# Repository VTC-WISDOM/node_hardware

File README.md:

# hardware
a collection of schematic and pcb designs for the WiSDOM node
unless otherwise specified, everything contained in this repository is licensed under the CERN Open Hardware License version 2 - Weakly Reciprocal License (CERN-OHL-W).
this is comparable to the gpl2, see LICENSE for details

## Using this repo
using your favorite package manager, install kicad-footprints and kicad-symbols alongside kicad. this is the best way to get the standard libraries. if you for some reason cannot do so, see the linked official kicad libraries in kicad-libs/footprints and kicad-libs/symbols.
in the kicad symbol editor, go to preferences -> manage symbol libraries and select "add existing", navigate to the kicad-libs/symbols directory and select the symbol libraries contained therein. repeat this with the symbols contained in kicad-libs/JLCPCB-Kicad-Library.
repeat this for footprints.

### node-rp2040
stores all of the relevant design files for the WiSDOM node that is based on the RP2040

### node-rp2350
like above but the RP2350

### other
test projects, antenna and transmission equipment, etc. anything unspecified

### docs
will add as much documentation as possible!

## Node V6 (RP2040)

changes:
- removed 5v regulator
- changed rp2040 xtal to the recommended part due to availability
- changed the sim card slot due to availability
- reviewed other parts and made changes to ensure full availability from both JLC and Digikey
- changed footprints over to JLC library footprints
- major layout changes- pin headers now broken out in two halves, etc - look at the pcb for a full description
- removed jst connectors (evil) and replaced them with barrel jacks
- mounting holes now m2.5 instead of m2

## Node V5 (RP2040)
 ***SIM7080G NON-FUNCTIONAL***

change since previous version:
- added USBLC6 esd protection on the usb line
- added CAT24 eeprom ic
- removed options for rtc to stick with just the PCF8523
- added SP3485 for RS485 / MODBUS communication
- added u.fl connector for the ism radio
- changed to narrower profile pushbuttons for run/bootsel
- added additional reset switch to interrupt 3.3V to the board entirely (used to reset the device to a known state for all components including the radios)
- yet more improvements to routing
- updated design to be mostly assembled by JLC pcb fab available components

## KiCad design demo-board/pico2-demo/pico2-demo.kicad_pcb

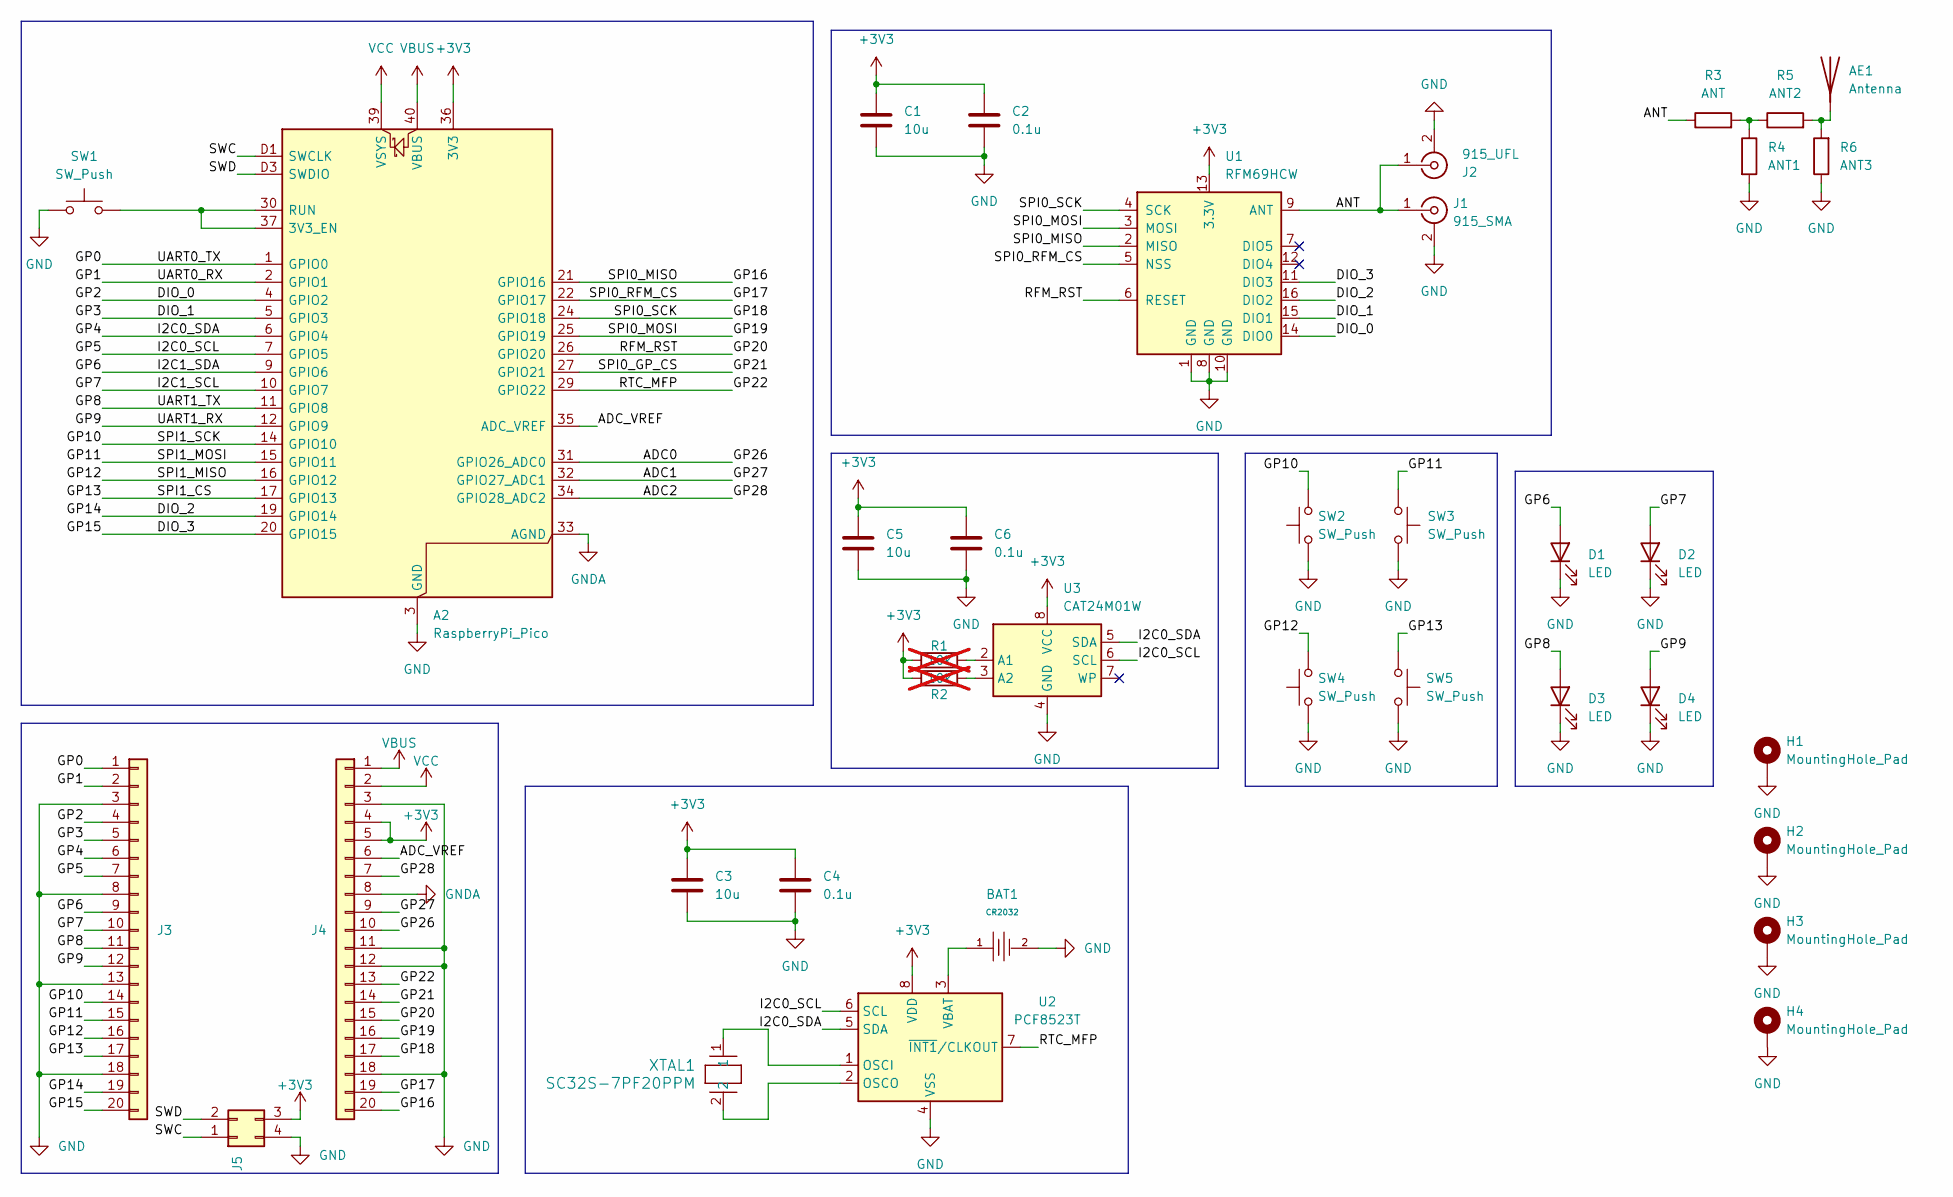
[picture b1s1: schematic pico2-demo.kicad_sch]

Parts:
A2: RaspberryPi_Pico; RaspberryPi_Pico_SMD_HandSolder
AE1: Antenna; Texas_SWRA416_868MHz_915MHz
BAT1: CR2032; BAT_BAT-HLD-001-THM; Part BS-07-A1BJ001; LCSC C2979167
C1, C3, C5: 10u; C_0805_2012Metric_Pad1.18x1.45mm_HandSolder
C2, C4, C6: 0.1u; C_0402_1005Metric_Pad0.74x0.62mm_HandSolder
D1, D2, D3, D4: LED; LED_1206_3216Metric_Pad1.42x1.75mm_HandSolder
H1, H2, H3: MountingHole_Pad; MountingHole_3.2mm_M3_Pad
H4: MountingHole_Pad; MountingHole_3.2mm_M3
J1: 915_SMA; SMA_Samtec_SMA-J-P-H-ST-EM1_EdgeMount
J2: 915_UFL; U.FL_Molex_MCRF_73412-0110_Vertical
J3, J4: Conn_01x20; PinHeader_1x20_P2.54mm_Vertical
J5: Conn_02x02_Counter_Clockwise; PinHeader_2x02_P2.54mm_Vertical
R1, R2: 10k; R_0805_2012Metric_Pad1.20x1.40mm_HandSolder; not fitted
R3: ANT; R_0805_2012Metric_Pad1.20x1.40mm_HandSolder
R4: ANT1; C_0402_1005Metric_Pad0.74x0.62mm_HandSolder
R5: ANT2; C_0402_1005Metric_Pad0.74x0.62mm_HandSolder
R6: ANT3; C_0402_1005Metric_Pad0.74x0.62mm_HandSolder
SW1, SW2, SW3, SW4, SW5: SW_Push; SW_PUSH_6mm
U1: RFM69HCW; HOPERF_RFM9XW_SMD
U2: PCF8523T; SOIC-8_3.9x4.9mm_P1.27mm
U3: CAT24M01W; SOIC-8_3.9x4.9mm_P1.27mm
XTAL1: SC32S-7PF20PPM; XTAL_SC32S-7PF20PPM_EPS

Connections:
+3V3: A2.36 (3V3), C1.1, C2.1, C3.1, C4.1, C5.1, C6.1, J4.4, J4.5, J5.3, R1.1, R2.1, U1.13 (3.3V), U2.8 (VDD), U3.8 (VCC)
/ADC0: A2.31 (GPIO26_ADC0), J4.10
/ADC1: A2.32 (GPIO27_ADC1), J4.9
/ADC2: A2.34 (GPIO28_ADC2), J4.7
/ADC_VREF: A2.35 (ADC_VREF), J4.6
/ANT: J1.1 (In), J2.1 (In), R3.1, U1.9 (ANT)
/DIO_0: A2.4 (GPIO2), J3.4, U1.14 (DIO0)
/DIO_1: A2.5 (GPIO3), J3.5, U1.15 (DIO1)
/DIO_2: A2.19 (GPIO14), J3.19, U1.16 (DIO2)
/DIO_3: A2.20 (GPIO15), J3.20, U1.11 (DIO3)
/GP0: A2.1 (GPIO0), J3.1
/GP1: A2.2 (GPIO1), J3.2
/GP4: A2.6 (GPIO4), J3.6, U2.5 (SDA), U3.5 (SDA)
/GP5: A2.7 (GPIO5), J3.7, U2.6 (SCL), U3.6 (SCL)
/GP6: A2.9 (GPIO6), D1.2 (A), J3.9
/GP7: A2.10 (GPIO7), D2.2 (A), J3.10
/GP8: A2.11 (GPIO8), D3.2 (A), J3.11
/GP9: A2.12 (GPIO9), D4.2 (A), J3.12
/GP10: A2.14 (GPIO10), J3.14, SW2.2
/GP11: A2.15 (GPIO11), J3.15, SW3.1
/GP12: A2.16 (GPIO12), J3.16, SW4.2
/GP13: A2.17 (GPIO13), J3.17, SW5.1
/GP16: A2.21 (GPIO16), J4.20, U1.2 (MISO)
/GP17: A2.22 (GPIO17), J4.19, U1.5 (NSS)
/GP18: A2.24 (GPIO18), J4.17, U1.4 (SCK)
/GP19: A2.25 (GPIO19), J4.16, U1.3 (MOSI)
/GP20: A2.26 (GPIO20), J4.15, U1.6 (RESET)
/GP21: A2.27 (GPIO21), J4.14
/GP22: A2.29 (GPIO22), J4.13, U2.7 (~INT1/CLKOUT)
/SWC: A2.D1 (SWCLK), J5.1
/SWD: A2.D3 (SWDIO), J5.2
GND: A2.3 (GND), A2.8 (GND), A2.13 (GND), A2.18 (GND), A2.23 (GND), A2.28 (GND), A2.38 (GND), A2.D2 (GND), BAT1.2, C1.2, C2.2, C3.2, C4.2, C5.2, C6.2, D1.1 (K), D2.1 (K), D3.1 (K), D4.1 (K), H1.1, H2.1, H3.1, J1.2 (Ext), J2.2 (Ext), J3.3, J3.8, J3.13, J3.18, J4.3, J4.11, J4.12, J4.18, J5.4, R4.2, R6.1, SW1.1, SW2.1, SW3.2, SW4.1, SW5.2, U1.1 (GND), U1.8 (GND), U1.10 (GND), U2.4 (VSS), U3.4 (GND)
GNDA: A2.33 (AGND), J4.8
unnamed: A2.30 (RUN), A2.37 (3V3_EN), SW1.2
unnamed: AE1.1 (A), R5.2, R6.2
unnamed: R3.2, R4.1, R5.1
unnamed: U2.1 (OSCI), XTAL1.1
unnamed: U2.2 (OSCO), XTAL1.2
unnamed: BAT1.1, U2.3 (VBAT)
unnamed: R1.2, U3.2 (A1)
unnamed: R2.2, U3.3 (A2)
VBUS: A2.40 (VBUS), J4.1
VCC: A2.39 (VSYS), J4.2

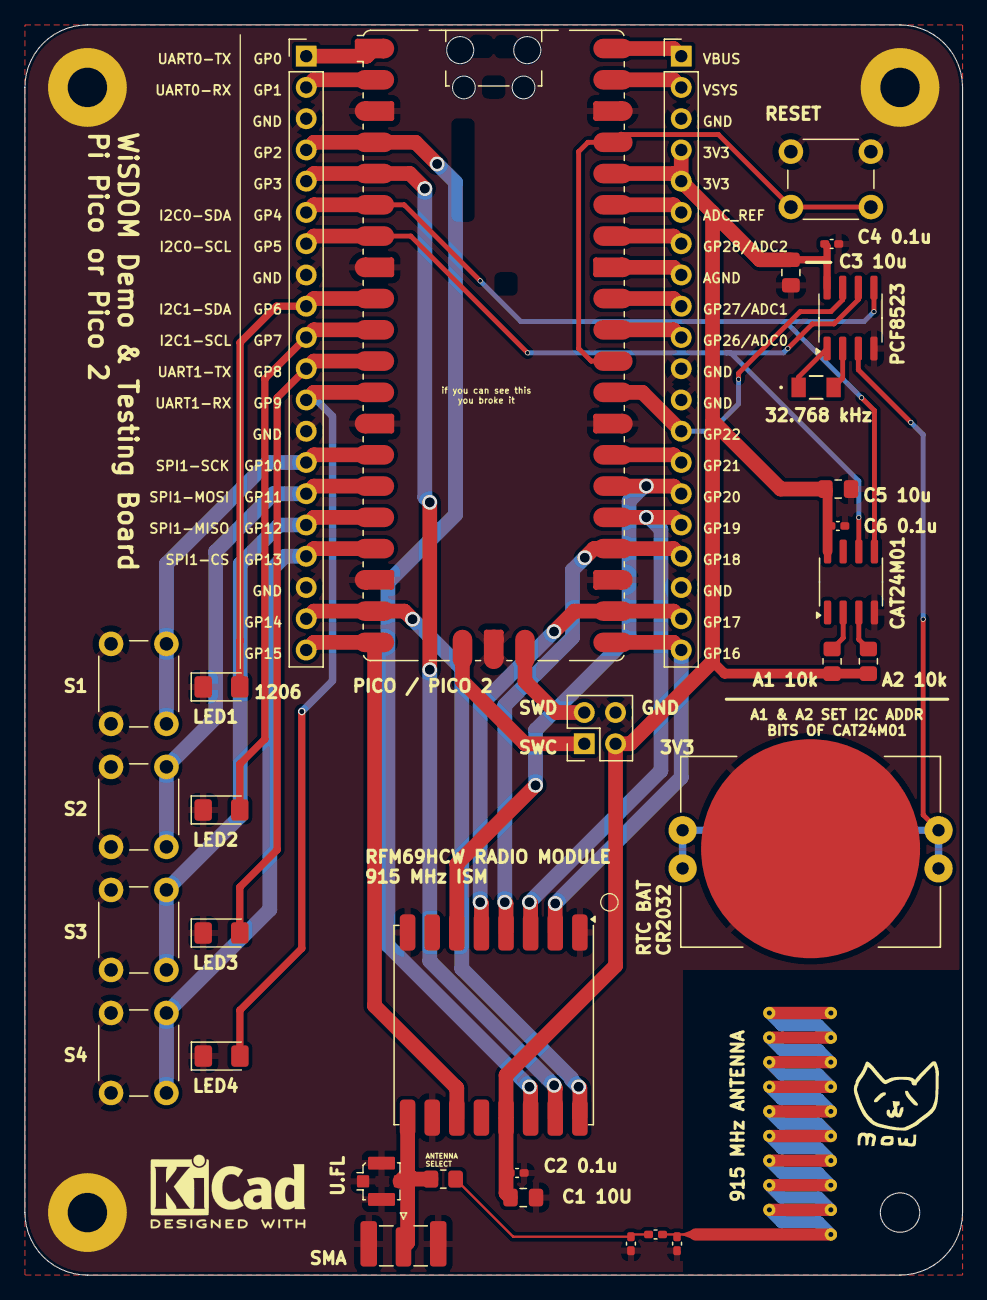
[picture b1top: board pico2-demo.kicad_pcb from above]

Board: 2 copper layers, 76.2 x 101.6 mm, 37 parts (0 on the bottom side), 43 nets.

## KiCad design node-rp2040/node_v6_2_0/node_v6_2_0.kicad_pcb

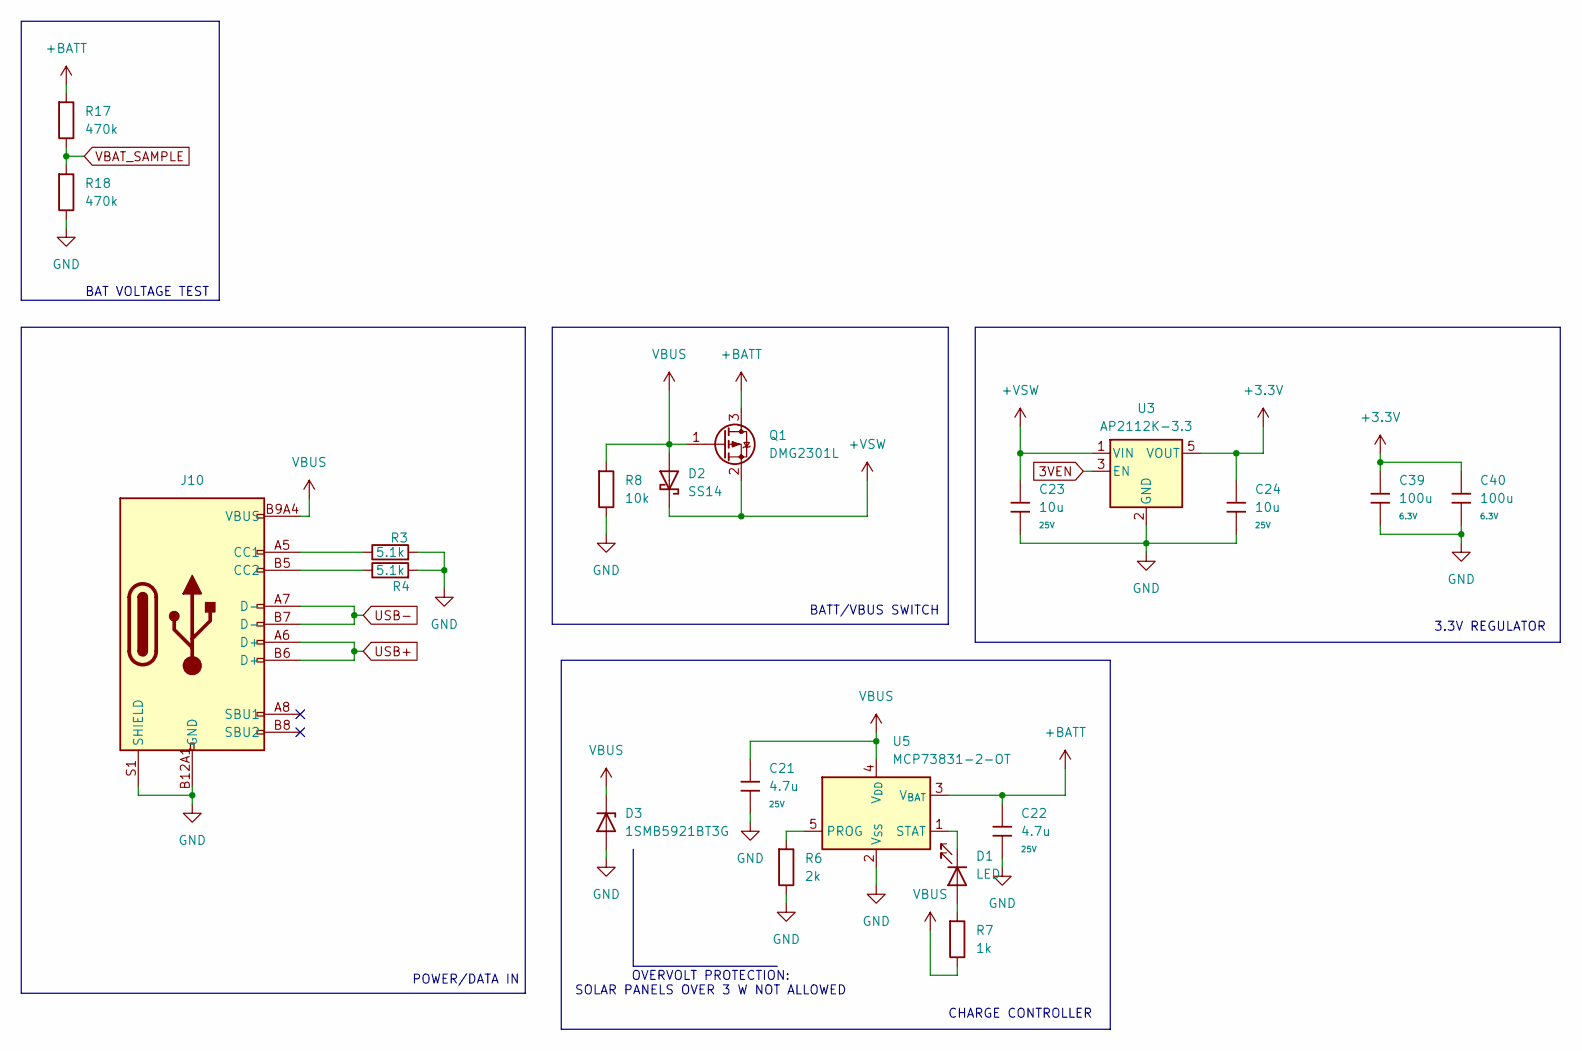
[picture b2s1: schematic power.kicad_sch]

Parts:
C21, C22: 4.7u; C_0805; Voltage Rated 25V; Tolerance ±10%; Part CL21A475KAQNNNE; LCSC C1779
C23, C24: 10u; C_0805; Voltage Rated 25V; Tolerance ±10%; Part CL21A106KAYNNNE; LCSC C15850
C39, C40: 100u; C_0805; Voltage Rated 6.3V; Tolerance ±20%; Part CL21A476MQYNNNE; LCSC C16780
D1: LED; LED_1206_3216Metric_Pad1.42x1.75mm_HandSolder
D2: SS14; D_SMA; Forward Voltage (Vf@If) 550mV@1A; Reverse Voltage (Vr) 40V; Part SS14; LCSC C2480
D3: 1SMB5921BT3G; D_SMB
J10: Connector, USB-TYPE-C-16P; TYPE-C-SMD_HX-TYPE-C-16PIN; LCSC C2927039
Q1: DMG2301L; D_SOT-23
R3, R4: 5.1k; R_0603
R6: 2k; R_0805; Overload Voltage (Max) 150V; Tolerance ±1%; Part 0805W8F2001T5E; LCSC C17604
R7: 1k; R_0805; Overload Voltage (Max) 150V; Tolerance ±1%; Part 0805W8F1001T5E; LCSC C17513
R8: 10k; R_0603; Overload Voltage (Max) 150V; Tolerance ±1%; Part 0805W8F1002T5E; LCSC C17414
R17, R18: 470k; R_0603; Overload Voltage (Max) 150V; Tolerance ±1%; Part 0805W8F4703T5E; LCSC C17709
U3: AP2112K-3.3; SOT-23-5_L3.0-W1.7-P0.95-LS2.8-BL
U5: MCP73831-2-OT; SOT-23-5_L3.0-W1.7-P0.95-LS2.8-BL

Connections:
3VEN: U3.3 (EN); also elsewhere on the board
+3.3V: C24.1, C39.1, C40.1, U3.5 (VOUT); also elsewhere on the board
+BATT: C22.1, Q1.3 (D), R17.1, U5.3 (V_{BAT}); also elsewhere on the board
+VSW: C23.1, D2.1, Q1.2 (S), U3.1 (VIN); also elsewhere on the board
GND: C21.2, C22.2, C23.2, C24.2, C39.2, C40.2, D3.2 (A), J10.A12B1 (GND), J10.B12A1 (GND), J10.S1 (SHIELD), R3.2, R4.2, R6.2, R8.2, R18.2, U3.2 (GND), U5.2 (V_{SS}); also elsewhere on the board
unnamed: D1.2 (A), R7.1
unnamed: D1.1 (K), U5.1 (STAT)
unnamed: J10.A5 (CC1), R3.1
unnamed: J10.B5 (CC2), R4.1
unnamed: R6.1, U5.5 (PROG)
USB+: J10.A6 (D+), J10.B6 (D+); also elsewhere on the board
USB-: J10.A7 (D-), J10.B7 (D-); also elsewhere on the board
VBAT_SAMPLE: R17.2, R18.1; also elsewhere on the board
VBUS: C21.1, D2.2, D3.1 (K), J10.A9B4 (VBUS), J10.B9A4 (VBUS), Q1.1 (G), R7.2, R8.1, U5.4 (V_{DD}); also elsewhere on the board

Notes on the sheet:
POWER/DATA IN
BATT/VBUS SWITCH
BAT VOLTAGE TEST
OVERVOLT PROTECTION: SOLAR PANELS OVER 3 W NOT ALLOWED
3.3V REGULATOR
CHARGE CONTROLLER

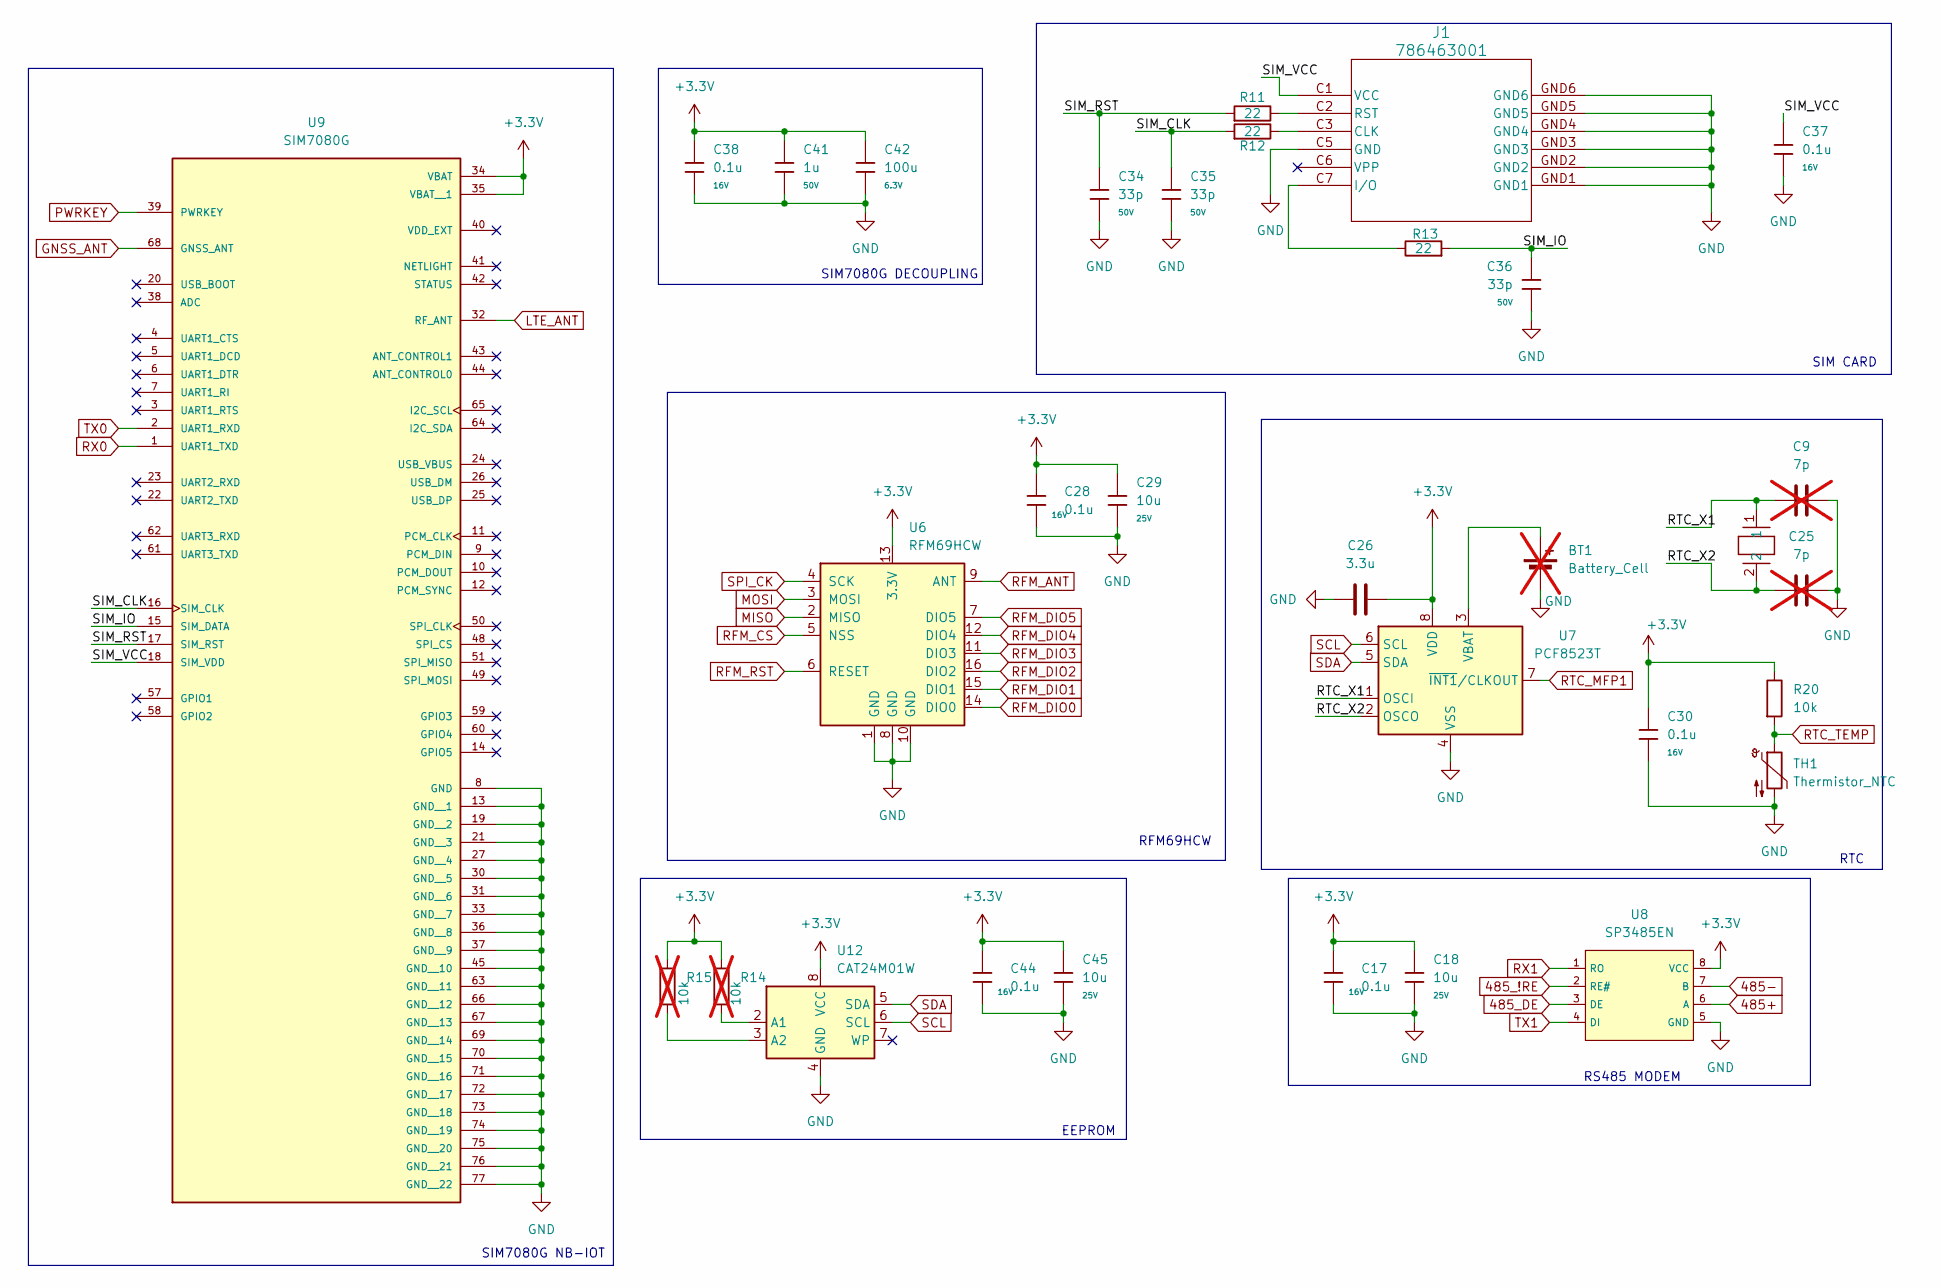
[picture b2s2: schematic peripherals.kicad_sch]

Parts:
BT1: Battery_Cell; BAT_BAT-HLD-001-THM; not fitted
C9, C25: 7p; C_0402; not fitted
C17, C28, C30, C37, C38, C44: 0.1u; C_0402; Voltage Rated 16V; Tolerance ±10%; Part CL05B104KO5NNNC; LCSC C1525
C18, C29, C45: 10u; C_0805; Voltage Rated 25V; Tolerance ±10%; Part CL21A106KAYNNNE; LCSC C15850
C26: 3.3u; C_0805
C34, C35, C36: 33p; C_0402; Voltage Rated 50V; Tolerance ±5%; Part 0402CG330J500NT; LCSC C1562
C41: 1u; C_0805; Voltage Rated 50V; Tolerance ±10%; Part CL21B105KBFNNNE; LCSC C28323
C42: 100u; C_0805; Voltage Rated 6.3V; Tolerance ±20%; Part CL21A476MQYNNNE; LCSC C16780
J1: 786463001; 78646-3001_MOL
R11, R12, R13: 22; R_0402; Overload Voltage (Max) 50V; Tolerance ±1%; Part 0402WGF220JTCE; LCSC C25092
R14, R15: 10k; R_0402; not fitted
R20: 10k; R_0402
TH1: Thermistor_NTC; R_0402
U6: RFM69HCW; HOPERF_RFM9XW_SMD
U7: PCF8523T; SOIC-8_3.9x4.9mm_P1.27mm
U8: SP3485EN; SOIC-8_L5.0-W4.0-P1.27-LS6.0-BL; Supply Voltage 3.3V; Part SP3485EN-L/TR; LCSC C8963
U9: SIM7080G; XCVR_SIM7080G; PARTREV 1.04
U12: CAT24M01W; SOIC-8_3.9x4.9mm_P1.27mm
XTAL1: SC32S-7PF20PPM; XTAL_SC32S-7PF20PPM_EPS

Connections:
485+: U8.6 (A); also elsewhere on the board
485-: U8.7 (B); also elsewhere on the board
485_!RE: U8.2 (RE#); also elsewhere on the board
485_DE: U8.3 (DE); also elsewhere on the board
+3.3V: C17.1, C18.1, C26.2, C28.1, C29.1, C30.1, C38.1, C41.1, C42.1, C44.1, C45.1, R14.1, R15.1, R20.1, U6.13 (3.3V), U7.8 (VDD), U8.8 (VCC), U9.34 (VBAT), U9.35 (VBAT__1), U12.8 (VCC); also elsewhere on the board
/PERIPHERALS/RTC_X1: C9.1, U7.1 (OSCI), XTAL1.1
/PERIPHERALS/RTC_X2: C25.1, U7.2 (OSCO), XTAL1.2
/PERIPHERALS/SIM_CLK: C35.1, R12.1, U9.16 (SIM_CLK)
/PERIPHERALS/SIM_IO: C36.1, R13.1, U9.15 (SIM_DATA)
/PERIPHERALS/SIM_RST: C34.1, R11.1, U9.17 (SIM_RST)
/PERIPHERALS/SIM_VCC: C37.1, J1.C1 (VCC), U9.18 (SIM_VDD)
GND: BT1.2 (-), C9.2, C17.2, C18.2, C25.2, C26.1, C28.2, C29.2, C30.2, C34.2, C35.2, C36.2, C37.2, C38.2, C41.2, C42.2, C44.2, C45.2, J1.C5 (GND), J1.GND1, J1.GND2, J1.GND3, J1.GND4, J1.GND5, J1.GND6, TH1.2, U6.1 (GND), U6.8 (GND), U6.10 (GND), U7.4 (VSS), U8.5 (GND), U9.8 (GND), U9.13 (GND__1), U9.19 (GND__2), U9.21 (GND__3), U9.27 (GND__4), U9.30 (GND__5), U9.31 (GND__6), U9.33 (GND__7), U9.36 (GND__8), U9.37 (GND__9), U9.45 (GND__10), U9.63 (GND__11), U9.66 (GND__12), U9.67 (GND__13), U9.69 (GND__14), U9.70 (GND__15), U9.71 (GND__16), U9.72 (GND__17), U9.73 (GND__18), U9.74 (GND__19), U9.75 (GND__20), U9.76 (GND__21), U9.77 (GND__22), U12.4 (GND); also elsewhere on the board
GNSS_ANT: U9.68 (GNSS_ANT); also elsewhere on the board
LTE_ANT: U9.32 (RF_ANT); also elsewhere on the board
MISO: U6.2 (MISO); also elsewhere on the board
MOSI: U6.3 (MOSI); also elsewhere on the board
unnamed: BT1.1 (+), U7.3 (VBAT)
unnamed: J1.C3 (CLK), R12.2
unnamed: J1.C7 (I/O), R13.2
unnamed: J1.C2 (RST), R11.2
unnamed: R14.2, U12.2 (A1)
unnamed: R15.2, U12.3 (A2)
PWRKEY: U9.39 (PWRKEY); also elsewhere on the board
RFM_ANT: U6.9 (ANT); also elsewhere on the board
RFM_CS: U6.5 (NSS); also elsewhere on the board
RFM_DIO0: U6.14 (DIO0); also elsewhere on the board
RFM_DIO1: U6.15 (DIO1); also elsewhere on the board
RFM_DIO2: U6.16 (DIO2); also elsewhere on the board
RFM_DIO3: U6.11 (DIO3); also elsewhere on the board
RFM_DIO4: U6.12 (DIO4); also elsewhere on the board
RFM_DIO5: U6.7 (DIO5); also elsewhere on the board
RFM_RST: U6.6 (RESET); also elsewhere on the board
RTC_MFP1: U7.7 (~INT1/CLKOUT); also elsewhere on the board
RTC_TEMP: R20.2, TH1.1; also elsewhere on the board
RX0: U9.1 (UART1_TXD); also elsewhere on the board
RX1: U8.1 (RO); also elsewhere on the board
SCL: U7.6 (SCL), U12.6 (SCL); also elsewhere on the board
SDA: U7.5 (SDA), U12.5 (SDA); also elsewhere on the board
SPI_CK: U6.4 (SCK); also elsewhere on the board
TX0: U9.2 (UART1_RXD); also elsewhere on the board
TX1: U8.4 (DI); also elsewhere on the board

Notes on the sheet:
RFM69HCW
EEPROM
SIM7080G DECOUPLING
RTC
SIM CARD
RS485 MODEM
SIM7080G NB-IOT

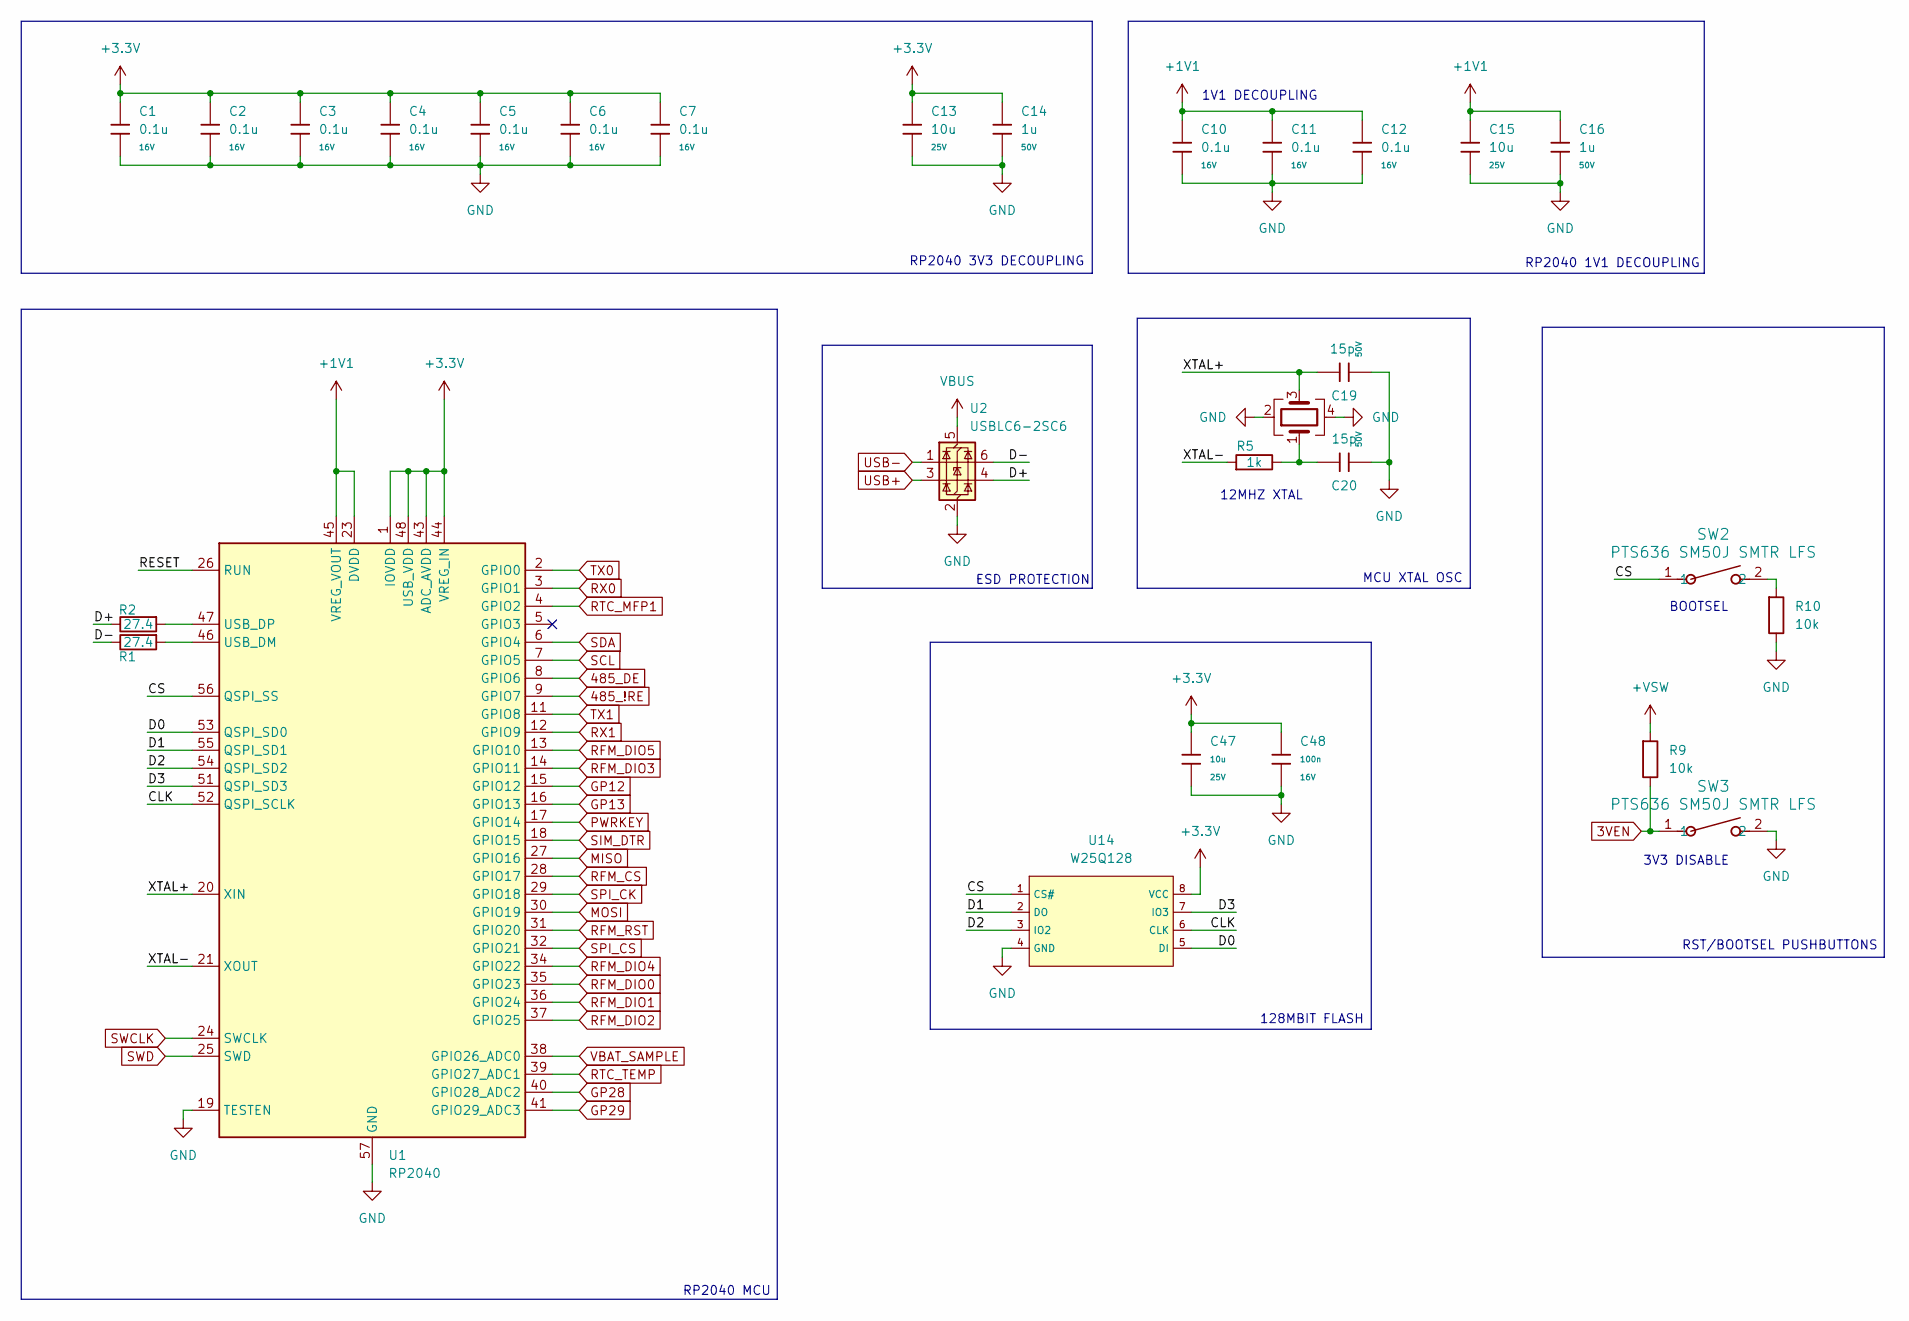
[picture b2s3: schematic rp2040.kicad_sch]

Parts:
C1, C2, C3, C4, C5, C6, C7, C10, C11, C12: 0.1u; C_0402; Voltage Rated 16V; Tolerance ±10%; Part CL05B104KO5NNNC; LCSC C1525
C13, C15, C47: 10u; C_0805; Voltage Rated 25V; Tolerance ±10%; Part CL21A106KAYNNNE; LCSC C15850
C14, C16: 1u; C_0805; Voltage Rated 50V; Tolerance ±10%; Part CL21B105KBFNNNE; LCSC C28323
C19, C20: 15p; C_0402; Voltage Rated 50V; Tolerance ±5%; Part 0402CG150J500NT; LCSC C1548
C48: 100n; C_0402; Voltage Rated 16V; Tolerance ±10%; Part CL05B104KO5NNNC; LCSC C1525
R1, R2: 27.4; R_0603; Overload Voltage (Max) 75V; Tolerance ±1%; Part 0603WAF270JT5E; LCSC C25190
R5: 1k; R_0402; Overload Voltage (Max) 150V; Tolerance ±1%; Part 0805W8F1001T5E; LCSC C17513
R9, R10: 10k; R_0805; Overload Voltage (Max) 150V; Tolerance ±1%; Part 0805W8F1002T5E; LCSC C17414
SW2, SW3: PTS636 SM50J SMTR LFS; SW_PTS636_CNK
U1: RP2040; QFN-56-1EP_7x7mm_P0.4mm_EP3.2x3.2mm_ThermalVias; LCSC C2040
U2: USBLC6-2SC6; SOT-23-6_L2.9-W1.6-P0.95-LS2.8-BL
U14: W25Q128; SOIC-8_L5.3-W5.3-P1.27-LS8.0-BL; Part W25Q128JVSIQ; LCSC C97521
Y1: ABM8-272-T3; CRYSTAL-SMD_4P-L3.2-W2.5-BL

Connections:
3VEN: R9.2, SW3.1; also elsewhere on the board
485_!RE: U1.9 (GPIO7); also elsewhere on the board
485_DE: U1.8 (GPIO6); also elsewhere on the board
+1V1: C10.1, C11.1, C12.1, C15.1, C16.1, U1.23 (DVDD), U1.45 (VREG_VOUT), U1.50 (DVDD)
+3.3V: C1.1, C2.1, C3.1, C4.1, C5.1, C6.1, C7.1, C13.1, C14.1, C47.1, C48.1, U1.1 (IOVDD), U1.10 (IOVDD), U1.22 (IOVDD), U1.33 (IOVDD), U1.42 (IOVDD), U1.43 (ADC_AVDD), U1.44 (VREG_IN), U1.48 (USB_VDD), U1.49 (IOVDD), U14.8 (VCC); also elsewhere on the board
+VSW: R9.1; also elsewhere on the board
/MCU/CLK: U1.52 (QSPI_SCLK), U14.6 (CLK)
/MCU/CS: SW2.1, U1.56 (QSPI_SS), U14.1 (CS#)
/MCU/D0: U1.53 (QSPI_SD0), U14.5 (DI)
/MCU/D1: U1.55 (QSPI_SD1), U14.2 (DO)
/MCU/D2: U1.54 (QSPI_SD2), U14.3 (IO2)
/MCU/D3: U1.51 (QSPI_SD3), U14.7 (IO3)
/MCU/D+: R2.2, U2.4 (I/O2)
/MCU/D-: R1.2, U2.6 (I/O1)
/MCU/RESET: U1.26 (RUN)
/MCU/XTAL+: C19.1, U1.20 (XIN), Y1.3
/MCU/XTAL-: R5.1, U1.21 (XOUT)
GND: C1.2, C2.2, C3.2, C4.2, C5.2, C6.2, C7.2, C10.2, C11.2, C12.2, C13.2, C14.2, C15.2, C16.2, C19.2, C20.2, C47.2, C48.2, R10.2, SW3.2, U1.19 (TESTEN), U1.57 (GND), U2.2 (GND), U14.4 (GND), Y1.2, Y1.4; also elsewhere on the board
GP12: U1.15 (GPIO12); also elsewhere on the board
GP13: U1.16 (GPIO13); also elsewhere on the board
GP28: U1.40 (GPIO28_ADC2); also elsewhere on the board
GP29: U1.41 (GPIO29_ADC3); also elsewhere on the board
MISO: U1.27 (GPIO16); also elsewhere on the board
MOSI: U1.30 (GPIO19); also elsewhere on the board
unnamed: C20.1, R5.2, Y1.1
unnamed: R10.1, SW2.2
unnamed: R1.1, U1.46 (USB_DM)
unnamed: R2.1, U1.47 (USB_DP)
PWRKEY: U1.17 (GPIO14); also elsewhere on the board
RFM_CS: U1.28 (GPIO17); also elsewhere on the board
RFM_DIO0: U1.35 (GPIO23); also elsewhere on the board
RFM_DIO1: U1.36 (GPIO24); also elsewhere on the board
RFM_DIO2: U1.37 (GPIO25); also elsewhere on the board
RFM_DIO3: U1.14 (GPIO11); also elsewhere on the board
RFM_DIO4: U1.34 (GPIO22); also elsewhere on the board
RFM_DIO5: U1.13 (GPIO10); also elsewhere on the board
RFM_RST: U1.31 (GPIO20); also elsewhere on the board
RTC_MFP1: U1.4 (GPIO2); also elsewhere on the board
RTC_TEMP: U1.39 (GPIO27_ADC1); also elsewhere on the board
RX0: U1.3 (GPIO1); also elsewhere on the board
RX1: U1.12 (GPIO9); also elsewhere on the board
SCL: U1.7 (GPIO5); also elsewhere on the board
SDA: U1.6 (GPIO4); also elsewhere on the board
SIM_DTR: U1.18 (GPIO15)
SPI_CK: U1.29 (GPIO18); also elsewhere on the board
SPI_CS: U1.32 (GPIO21); also elsewhere on the board
SWCLK: U1.24 (SWCLK); also elsewhere on the board
SWD: U1.25 (SWD); also elsewhere on the board
TX0: U1.2 (GPIO0); also elsewhere on the board
TX1: U1.11 (GPIO8); also elsewhere on the board
USB+: U2.3 (I/O2); also elsewhere on the board
USB-: U2.1 (I/O1); also elsewhere on the board
VBAT_SAMPLE: U1.38 (GPIO26_ADC0); also elsewhere on the board
VBUS: U2.5 (VBUS); also elsewhere on the board

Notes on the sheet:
RST/BOOTSEL PUSHBUTTONS
RP2040 3V3 DECOUPLING
RP2040 MCU
RP2040 1V1 DECOUPLING
BOOTSEL
3V3 DISABLE
MCU XTAL OSC
1V1 DECOUPLING
12MHZ XTAL
128MBIT FLASH
ESD PROTECTION

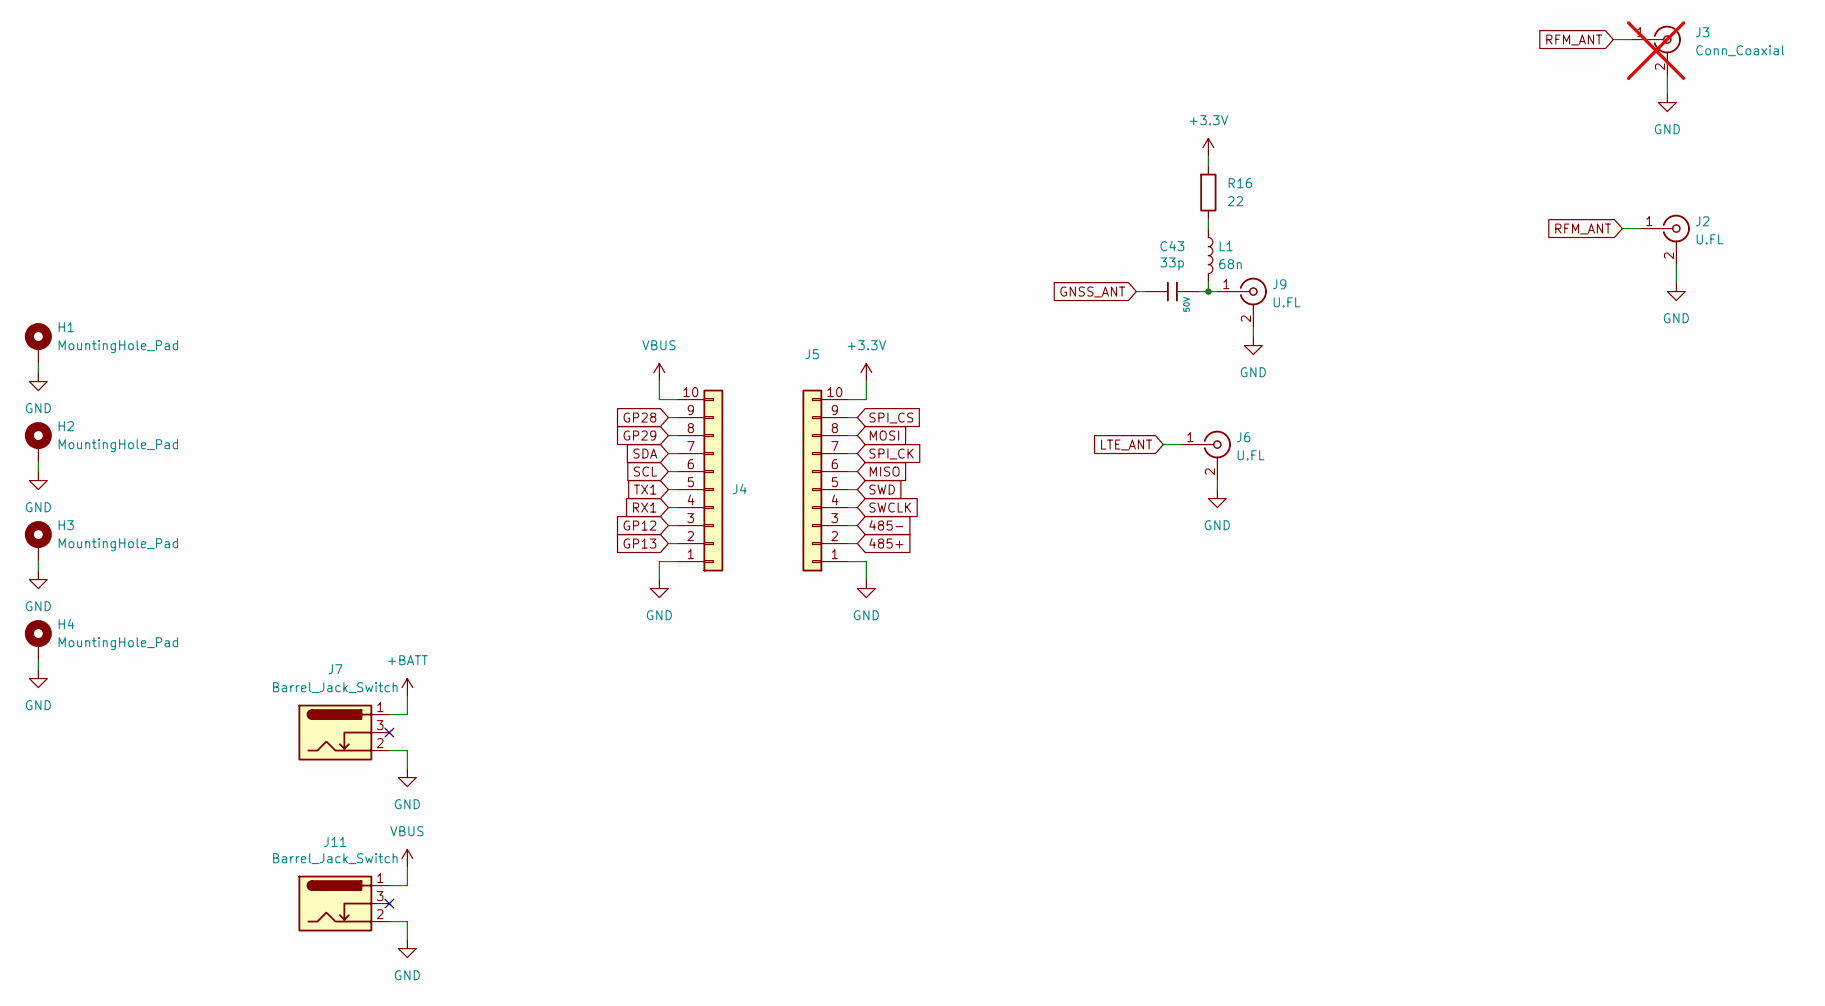
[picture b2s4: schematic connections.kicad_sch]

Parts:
C43: 33p; C_0402; Voltage Rated 50V; Tolerance ±5%; Part 0402CG330J500NT; LCSC C1562
H1, H2, H3, H4: MountingHole_Pad; MountingHole_2.5mm_Pad_TopBottom
J2, J6, J9: U.FL; IPEX-SMD_BWIPX-1-001E; LCSC C5137195
J3: Conn_Coaxial; SMA_Samtec_SMA-J-P-H-ST-EM1_EdgeMount; not fitted
J4, J5: Conn_01x10; PinHeader_1x10_P2.54mm_Vertical
J7, J11: Barrel_Jack_Switch; PJ-007
L1: 68n; L_0402
R16: 22; R_0402; Overload Voltage (Max) 150V; Tolerance ±1%; Part 0805W8F220JT5E; LCSC C17561

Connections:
485+: J5.2; also elsewhere on the board
485-: J5.3; also elsewhere on the board
+3.3V: J5.10, R16.1; also elsewhere on the board
+BATT: J7.1; also elsewhere on the board
GND: H1.1, H2.1, H3.1, H4.1, J2.2 (Ext), J2.3, J3.2 (Ext), J4.1, J5.1, J6.2 (Ext), J6.3, J7.2, J9.2 (Ext), J9.3, J11.2; also elsewhere on the board
GNSS_ANT: C43.1; also elsewhere on the board
GP12: J4.3; also elsewhere on the board
GP13: J4.2; also elsewhere on the board
GP28: J4.9; also elsewhere on the board
GP29: J4.8; also elsewhere on the board
LTE_ANT: J6.1 (In); also elsewhere on the board
MISO: J5.6; also elsewhere on the board
MOSI: J5.8; also elsewhere on the board
unnamed: C43.2, J9.1 (In), L1.2
unnamed: L1.1, R16.2
RFM_ANT: J2.1 (In), J3.1 (In); also elsewhere on the board
RX1: J4.4; also elsewhere on the board
SCL: J4.6; also elsewhere on the board
SDA: J4.7; also elsewhere on the board
SPI_CK: J5.7; also elsewhere on the board
SPI_CS: J5.9; also elsewhere on the board
SWCLK: J5.4; also elsewhere on the board
SWD: J5.5; also elsewhere on the board
TX1: J4.5; also elsewhere on the board
VBUS: J4.10, J11.1; also elsewhere on the board
